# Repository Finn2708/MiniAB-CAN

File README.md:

# MiniAB-CAN
Toolhead board with CAN interface for [Voron Mini Afterburner](https://github.com/VoronDesign/Voron-0) and [Voron Stealthburner](https://github.com/VoronDesign/Voron-Afterburner/tree/sb-beta).

Features:
- CAN bus interface
- TMC2209 stepper driver for extruder motor
- Integrated ADXL345 for resonance compensation
- Neopixel Output for toolhead LEDs
- Two endstop and one probe port
- User-selectable fan voltages (5V/24V)

---

## Table of Contents
- [Prototype](#prototype)
  - [Size comparison](#size)
  - [Thermal images](#thermal-images)
- [Pinout](#pinout)
- [Interactive BOM](https://finn2708.github.io/MiniAB-CAN/index.html)

## Prototype

### Size

### Thermal images

## Pinout

## BOM
[Interactive BOM](https://finn2708.github.io/MiniAB-CAN/index.html)

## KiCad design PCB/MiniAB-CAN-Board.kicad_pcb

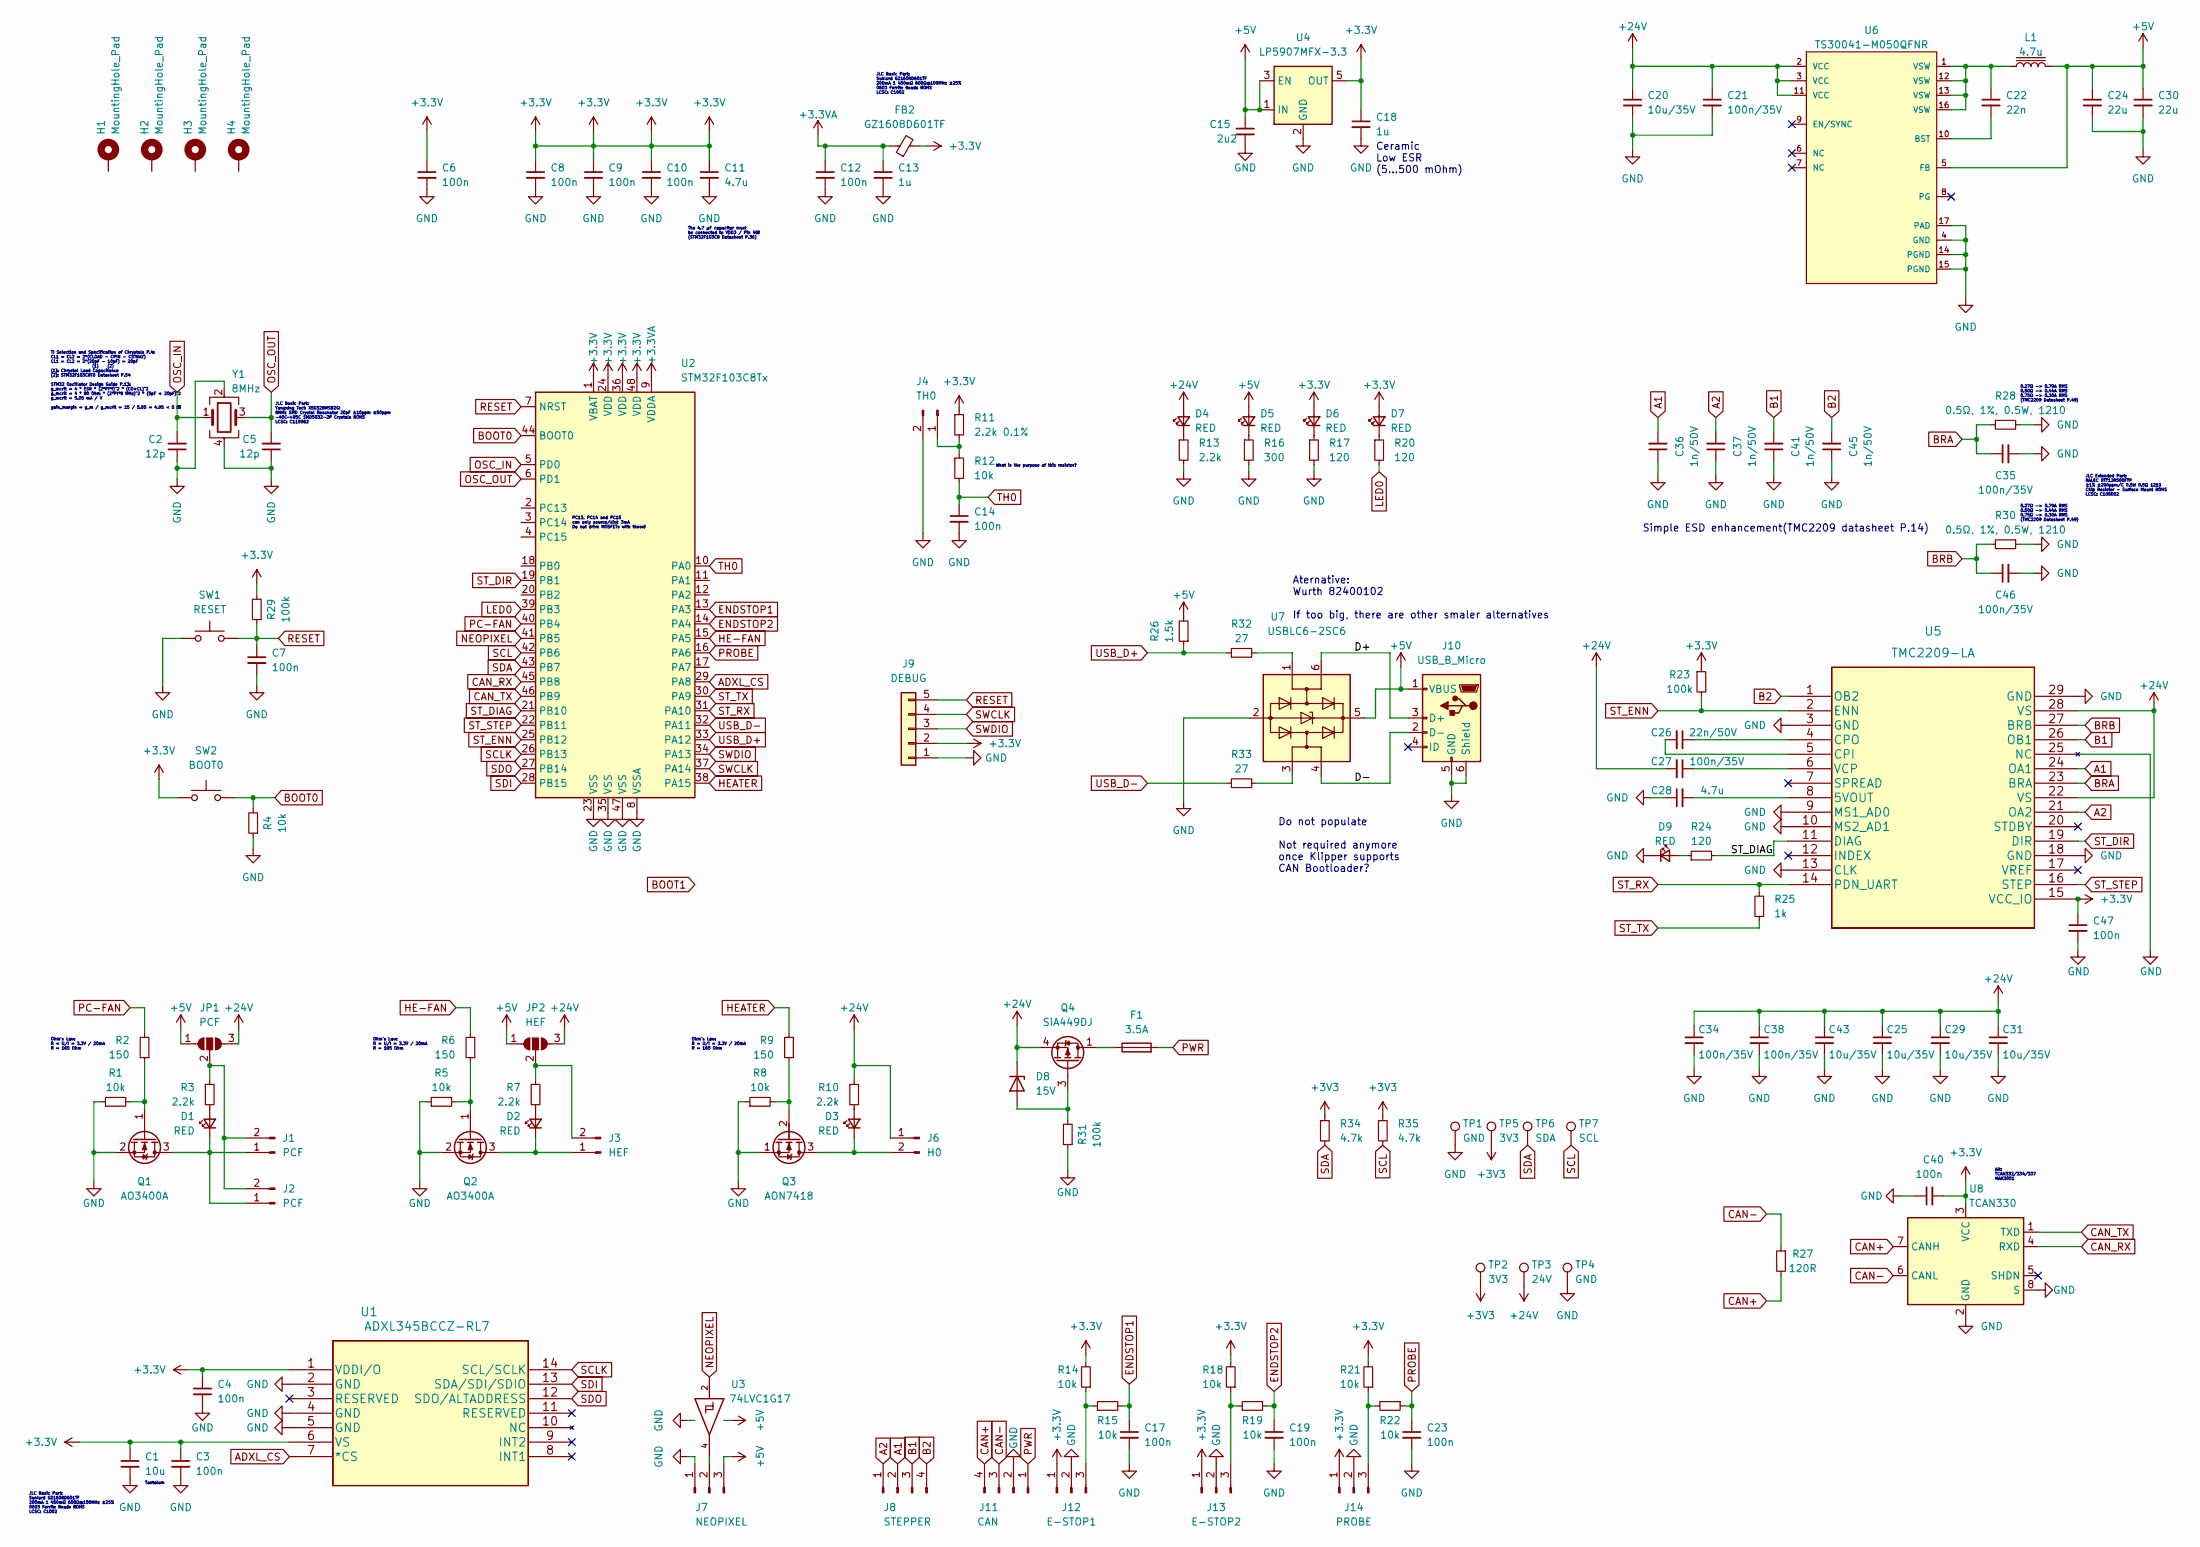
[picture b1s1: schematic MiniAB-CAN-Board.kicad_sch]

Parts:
C1: 10u; CP_EIA-3216-18_Kemet-A; MFG# TAJA106K016RNJ; LCSC# C7171
C2, C5: 12p; C_0402_1005Metric; MFG# C1005NP0120KGT; LCSC# C258502
C3, C4, C6, C7, C8, C9, C10, C12, C14, C17, C19, C23, C40, C47: 100n; C_0402_1005Metric; MFG# CL05B104KB54PNC; LCSC# C307331
C11, C28: 4.7u; C_0402_1005Metric; MFG# C0402X5R475M250NT; LCSC# C2911388
C13, C18: 1u; C_0402_1005Metric; MFG# CL05A105KA5NQNC; LCSC# C52923
C15: 2u2; C_0402_1005Metric; MFG# GRT155C71A225KE13D; LCSC# C415540
C20: 10u/35V; C_1206_3216Metric; MFG# GMK316AB7106KL-TR; LCSC# C454102
C21, C27, C34, C35, C38, C46: 100n/35V; C_0402_1005Metric; MFG# CL05B104KB54PNC; LCSC# C307331
C22: 22n; C_0402_1005Metric; MFG# CC0402KRX7R9BB223; LCSC# C107026
C24, C30: 22u; C_1206_3216Metric; MFG# C1206X7R226K160NT
C25, C29, C31, C43: 10u/35V; C_0805_2012Metric; MFG# C2012X5R1V226MT000E; LCSC# C338080
C26: 22n/50V; C_0402_1005Metric; MFG# 0402B223K500NT; LCSC# C1532
C36, C37, C41, C45: 1n/50V; C_0402_1005Metric; MFG# C0402C102K5RACAUTO; LCSC# C141053
D1, D2, D3, D4, D5, D6, D7, D9: RED; LED_0402_1005Metric
D8: 15V; D_SOD-323; MFG# SZMM3Z15VT1G; LCSC# C327522
F1: 3.5A; Fuse_0805_2012Metric; MFG# MFU0805FF03500P100; LCSC# C1972476
FB2: GZ1608D601TF; R_0603_1608Metric
H1, H2, H3, H4: MountingHole_Pad; MountingHole_3.2mm_M3_Pad_Via
J1, J2: PCF; JST_PH_B2B-PH-K_1x02_P2.00mm_Vertical
J3: HEF; JST_PH_B2B-PH-K_1x02_P2.00mm_Vertical
J4: TH0; JST_PH_B2B-PH-K_1x02_P2.00mm_Vertical
J6: H0; Molex_Micro-Fit_3.0_43045-0200_2x01_P3.00mm_Horizontal
J7: NEOPIXEL; JST_PH_B3B-PH-K_1x03_P2.00mm_Vertical
J8: STEPPER; JST_PH_B4B-PH-K_1x04_P2.00mm_Vertical
J9: DEBUG; PinHeader_1x05_P1.27mm_Vertical
J10: USB_B_Micro; USB_Micro-B_Amphenol_10118194_Horizontal
J11: CAN; Molex_Micro-Fit_3.0_43045-0400_2x02_P3.00mm_Horizontal
J12: E-STOP1; JST_PH_B3B-PH-K_1x03_P2.00mm_Vertical
J13: E-STOP2; JST_PH_B3B-PH-K_1x03_P2.00mm_Vertical
J14: PROBE; JST_PH_B3B-PH-K_1x03_P2.00mm_Vertical
JP1: PCF; SolderJumper-3_P1.3mm_Open_RoundedPad1.0x1.5mm_NumberLabels
JP2: HEF; SolderJumper-3_P1.3mm_Open_RoundedPad1.0x1.5mm_NumberLabels
L1: 4.7u; L_Coilcraft_XxL4020; MFG# MAPM0420F-4R7M-LF; LCSC# C280916
Q1, Q2: AO3400A; SOT-23
Q3: AON7418; MFG# AON7418; LCSC# C74384
Q4: SiA449DJ; Vishay_PowerPAK_SC70-6L_Single; MFG# SIA483DJ-T1-GE3; LCSC# C145467
R1, R4, R5, R8, R12, R14, R15, R18, R19, R21, R22: 10k; R_0402_1005Metric
R2, R6, R9: 150; R_0402_1005Metric
R3, R7, R10, R13: 2.2k; R_0402_1005Metric
R11: 2.2k 0.1%; R_0402_1005Metric
R16: 300; R_0402_1005Metric
R17, R20, R24: 120; R_0402_1005Metric
R23, R29, R31: 100k; R_0402_1005Metric
R25: 1k; R_0402_1005Metric
R26: 1.5k; R_0402_1005Metric; MFG# 0402WGJ0152TCE; LCSC# C25930
R27: 120R; R_0402_1005Metric; MFG# 0402WGF1200TCE; LCSC# C25079
R28, R30: 0.5Ω, 1%, 0.5W, 1210; R_0805_2012Metric
R32, R33: 27; R_0402_1005Metric; MFG# ERJ2RKF27R0X; LCSC# C413051
R34, R35: 4.7k; R_0402_1005Metric
SW1: RESET; SW_SPST_B3U-1000P; MFG# B3U-1000P; LCSC# C231329
SW2: BOOT0; SW_SPST_B3U-1000P; MFG# B3U-1000P; LCSC# C231329
TP1, TP4: GND; TestPoint_Pad_D1.0mm
TP2, TP5: 3V3; TestPoint_Pad_D1.0mm
TP3: 24V; TestPoint_Pad_D1.0mm
TP6: SDA; TestPoint_Pad_D1.0mm
TP7: SCL; TestPoint_Pad_D1.0mm
U1: ADXL345BCCZ-RL7
U2: STM32F103C8Tx; LQFP-48_7x7mm_P0.5mm
U3: 74LVC1G17; SOT-23-5
U4: LP5907MFX-3.3; SOT-23-5
U5: TMC2209-LA
U6: TS30041-M050QFNR; Semtech-QFN16-0-0-0; output voltage 5V; mouser part number 947-TS30041-M050QFNR; digikey description IC REG BUCK 5V 1A SYNC 16-VQFN
U7: USBLC6-2SC6; SOT-23-6; MFG# USBLC6-2SC6; LCSC# C7519
U8: TCAN330; TSOT-23-8
Y1: 8MHz; Crystal_SMD_3225-4Pin_3.2x2.5mm; MFG# TAXM8M4RFDCET2T; LCSC# C403948

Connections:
+3.3VA: C12.1, C13.1, FB2.1, U2.9 (VDDA)
+5V: C15.1, C24.1, C30.1, D5.2 (A), J7.3, J10.1 (VBUS), JP1.1 (A), JP2.1 (A), L1.2, R26.2, U3.5 (VCC), U4.1 (IN), U4.3 (EN), U6.5 (FB), U7.5 (VBUS)
+24V: C20.1, C21.1, C25.1, C27.2, C29.1, C31.1, C34.1, C38.1, C43.1, D4.2 (A), D8.1 (K), J6.1, JP1.3 (B), JP2.3 (B), Q4.4 (S), R10.1, TP3.1, U5.22 (VS), U5.28 (VS), U6.2 (VCC), U6.3 (VCC), U6.11 (VCC)
/D+: J10.3 (D+), U7.6 (I/O1)
/D-: J10.2 (D-), U7.4 (I/O2)
A1: C36.2, J8.2, U5.24 (OA1)
A2: C37.2, J8.1, U5.21 (OA2)
ADXL_CS: U1.7 (*CS), U2.29 (PA8)
B1: C41.2, J8.3, U5.26 (OB1)
B2: C45.2, J8.4, U5.1 (OB2)
BOOT0: R4.2, SW2.2, U2.44 (BOOT0)
BRA: C35.1, R28.2, U5.23 (BRA)
BRB: C46.1, R30.2, U5.27 (BRB)
CAN+: J11.4, R27.2, U8.7 (CANH)
CAN-: J11.3, R27.1, U8.6 (CANL)
CAN_RX: U2.45 (PB8), U8.4 (RXD)
CAN_TX: U2.46 (PB9), U8.1 (TXD)
ENDSTOP1: C17.1, R15.2, U2.13 (PA3)
ENDSTOP2: C19.1, R19.2, U2.14 (PA4)
GND: C1.2, C2.1, C3.2, C4.2, C5.1, C6.2, C7.2, C8.2, C9.2, C10.2, C11.2, C12.2, C13.2, C14.2, C15.2, C17.2, C18.2, C19.2, C20.2, C21.2, C23.2, C24.2, C25.2, C28.1, C29.2, C30.2, C31.2, C34.2, C35.2, C36.1, C37.1, C38.2, C40.1, C41.1, C43.2, C45.1, C46.2, C47.2, D9.1 (K), J4.2, J7.1, J9.1, J10.5 (GND), J10.6 (Shield), J11.2, J12.2, J13.2, J14.2, Q1.2 (S), Q2.2 (S), Q3.1 (S), R1.1, R4.1, R5.1, R8.1, R13.2, R16.2, R17.2, R28.1, R30.1, R31.1, SW1.1, TP1.1, TP4.1, U1.2 (GND), U1.4 (GND), U1.5 (GND), U2.8 (VSSA), U2.23 (VSS), U2.35 (VSS), U2.47 (VSS), U3.3 (GND), U4.2 (GND), U5.3 (GND), U5.9 (MS1_AD0), U5.10 (MS2_AD1), U5.13 (CLK), U5.18 (GND), U5.25 (NC), U5.29 (GND), U6.4 (GND), U6.14 (PGND), U6.15 (PGND), U6.17 (PAD), U7.2 (GND), U8.2 (GND), U8.8 (S), Y1.2, Y1.4
HE-FAN: R6.2, U2.15 (PA5)
HEATER: R9.2, U2.38 (PA15)
LED0: R20.2, U2.39 (PB3)
NEOPIXEL: U2.41 (PB5), U3.2
unnamed: C22.1, L1.1, U6.1 (VSW), U6.12 (VSW), U6.13 (VSW), U6.16 (VSW)
unnamed: C22.2, U6.10 (BST)
unnamed: C26.1, U5.4 (CPO)
unnamed: C26.2, U5.5 (CPI)
unnamed: C27.1, U5.6 (VCP)
unnamed: C28.2, U5.8 (5VOUT)
unnamed: D1.1 (K), J1.1, J2.1, Q1.3 (D)
unnamed: D1.2 (A), R3.2
unnamed: D2.1 (K), J3.1, Q2.3 (D)
unnamed: D2.2 (A), R7.2
unnamed: D3.1 (K), J6.2, Q3.3 (D)
unnamed: D3.2 (A), R10.2
unnamed: D4.1 (K), R13.1
unnamed: D5.1 (K), R16.1
unnamed: D6.1 (K), R17.1
unnamed: D7.1 (K), R20.1
unnamed: D8.2 (A), Q4.3 (G), R31.2
unnamed: D9.2 (A), R24.1
unnamed: F1.1, Q4.1 (D)
unnamed: J1.2, J2.2, JP1.2 (C), R3.1
unnamed: J3.2, JP2.2 (C), R7.1
unnamed: J4.1, R11.2, R12.1
unnamed: J7.2, U3.4
unnamed: J12.3, R14.1, R15.1
unnamed: J13.3, R18.1, R19.1
unnamed: J14.3, R21.1, R22.2
unnamed: Q1.1 (G), R1.2, R2.1
unnamed: Q2.1 (G), R5.2, R6.1
unnamed: Q3.2 (G), R8.2, R9.1
unnamed: R32.2, U7.1 (I/O1)
unnamed: R33.2, U7.3 (I/O2)
OSC_IN: C2.2, U2.5 (PD0), Y1.1
OSC_OUT: C5.2, U2.6 (PD1), Y1.3
PC-FAN: R2.2, U2.40 (PB4)
PROBE: C23.1, R22.1, U2.16 (PA6)
PWR: F1.2, J11.1
RESET: C7.1, J9.5, R29.1, SW1.2, U2.7 (NRST)
SCL: R35.2, TP7.1, U2.42 (PB6)
SCLK: U1.14 (SCL/SCLK), U2.26 (PB13)
SDA: R34.2, TP6.1, U2.43 (PB7)
SDI: U1.13 (SDA/SDI/SDIO), U2.28 (PB15)
SDO: U1.12 (SDO/ALTADDRESS), U2.27 (PB14)
ST_DIAG: R24.2, U2.21 (PB10), U5.11 (DIAG)
ST_DIR: U2.19 (PB1), U5.19 (DIR)
ST_ENN: R23.2, U2.25 (PB12), U5.2 (ENN)
ST_RX: R25.2, U2.31 (PA10), U5.14 (PDN_UART)
ST_STEP: U2.22 (PB11), U5.16 (STEP)
ST_TX: R25.1, U2.30 (PA9)
SWCLK: J9.4, U2.37 (PA14)
SWDIO: J9.3, U2.34 (PA13)
TH0: C14.1, R12.2, U2.10 (PA0)
USB_D+: R26.1, R32.1, U2.33 (PA12)
USB_D-: R33.1, U2.32 (PA11)

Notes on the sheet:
Ohm's Law: R = U/I = 3.3V / 20mA R = 165 Ohm
Do not populate Not required anymore once Klipper supports CAN Bootloader?
What is the purpose of this resistor?
0.27Ω -> 0.79A RMS 0.50Ω -> 0.44A RMS 0.75Ω -> 0.30A RMS (TMC2209 Datasheet P.49)
The 4.7 µF capacitor must be connected to VDD3 / Pin 48! (STM32F103C8 Datasheet P.36)
Alt: TCAN332/334/337 MAX3051
Tantalum
Aternative: Wurth 82400102 If too big, there are other smaler alternatives
JLC Basic Part: Sunlord GZ1608D601TF 200mA 1 450mΩ 600Ω@100MHz ±25% 0603 Ferrite Beads ROHS LCSC: C1002
PC13, PC14 and PC15 can only source/sink 3mA Do not drive MOSFETs with these!
Ceramic Low ESR (5...500 mOhm)
JLC Extended Part: RALEC RTT12R500FTP ±1% ±200ppm/C 0.5W 0.5Ω 1210 Chip Resistor - Surface Mount ROHS LCSC: C105052
TI Selection and Specification of Chrystals P.4: CL1 = CL2 = 2*(CLOAD - CPIN - CSTRAY) CL1 = CL2 = 2*(20pF - 10pF) = 20pF (1) (2) (1): Chrystal Load Capacitance (2): STM32F103C8T6 Datasheet P.54 STM32 Oscillator Design Guide P.13: g_mcrit = 4 * ESR * (2*PI*f)^2 * (C0+CL)^2 g_mcrit = 4 * 80 Ohm * (2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
JLC Basic Part: Yangxing Tech X50328MSB2GI 8MHz SMD Crystal Resonator 20pF ±10ppm ±50ppm -40C~+85C SMD5032-2P Crystals ROHS LCSC: C115962
Simple ESD enhancement(TMC2209 datasheet P.14)

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
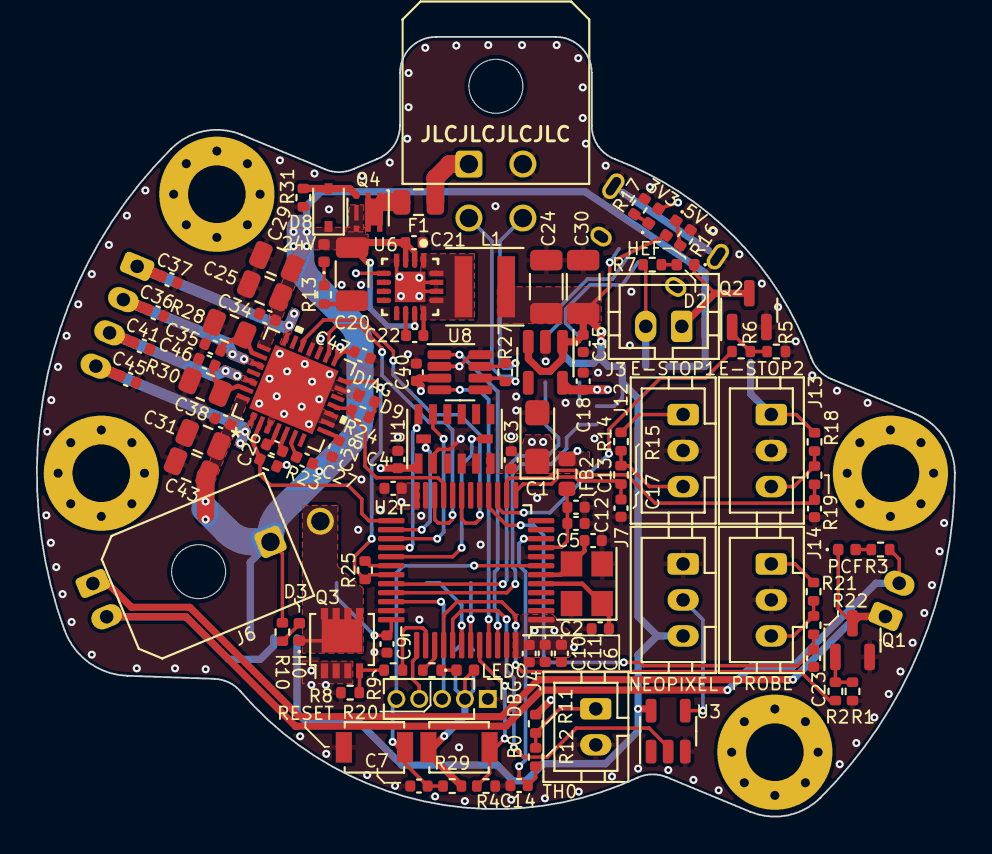
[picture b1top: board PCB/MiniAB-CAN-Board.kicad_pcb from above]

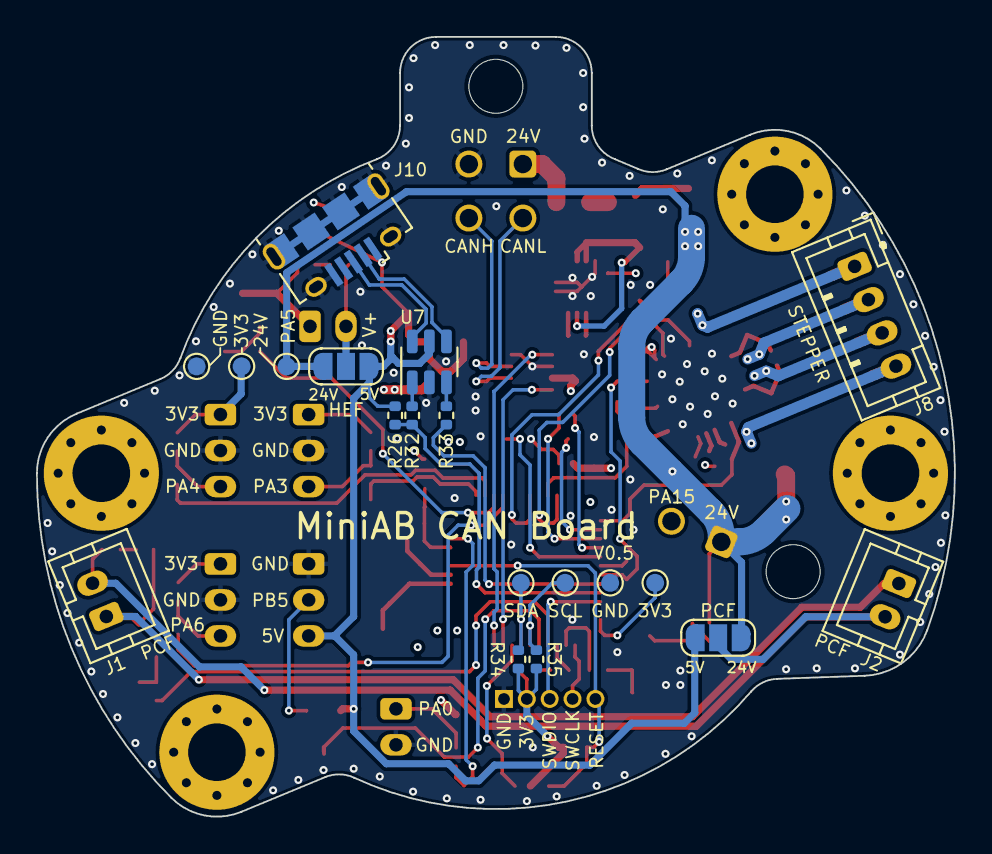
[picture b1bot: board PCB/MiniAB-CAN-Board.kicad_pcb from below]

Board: 4 copper layers, 51.0 x 43.3 mm, 129 parts (19 on the bottom side), 78 nets.

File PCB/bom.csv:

Comment,Designator,Footprint,LCSC
10u,C1,Capacitor_Tantalum_SMD:CP_EIA-3216-18_Kemet-A,
12p,"C2,C5",Capacitor_SMD:C_0402_1005Metric,
100n,"C3,C4,C6,C7,C8,C9,C10,C12,C14,C17,C19,C23,C40,C47",Capacitor_SMD:C_0402_1005Metric,
4.7u,"C11,C28",Capacitor_SMD:C_0402_1005Metric,
1u,"C13,C18",Capacitor_SMD:C_0402_1005Metric,
2u2,C15,Capacitor_SMD:C_0402_1005Metric,
10u/35V,C20,Capacitor_SMD:C_1206_3216Metric,
100n/35V,"C21,C27,C34,C35,C38,C46",Capacitor_SMD:C_0402_1005Metric,
22n,C22,Capacitor_SMD:C_0402_1005Metric,
22u,"C24,C30",Capacitor_SMD:C_1206_3216Metric,
10u/35V,"C25,C29,C31,C43",Capacitor_SMD:C_0805_2012Metric,
22n/50V,C26,Capacitor_SMD:C_0402_1005Metric,
1n/50V,"C36,C37,C41,C45",Capacitor_SMD:C_0402_1005Metric,
RED,"D1,D2,D3,D4,D5,D6,D7,D9",LED_SMD:LED_0402_1005Metric,
15V,D8,Diode_SMD:D_SOD-323,
3.5A,F1,Fuse:Fuse_0805_2012Metric,
GZ1608D601TF,FB2,Resistor_SMD:R_0603_1608Metric,
PCF,"J1,J2",Connector_JST:JST_PH_B2B-PH-K_1x02_P2.00mm_Vertical,
HEF,J3,Connector_JST:JST_PH_B2B-PH-K_1x02_P2.00mm_Vertical,
TH0,J4,Connector_JST:JST_PH_B2B-PH-K_1x02_P2.00mm_Vertical,
H0,J6,Connector_Molex:Molex_Micro-Fit_3.0_43045-0200_2x01_P3.00mm_Horizontal,
NEOPIXEL,J7,Connector_JST:JST_PH_B3B-PH-K_1x03_P2.00mm_Vertical,
STEPPER,J8,Connector_JST:JST_PH_B4B-PH-K_1x04_P2.00mm_Vertical,
DEBUG,J9,Connector_PinHeader_1.27mm:PinHeader_1x05_P1.27mm_Vertical,
USB_B_Micro,J10,Connector_USB:USB_Micro-B_Amphenol_10118194_Horizontal,
CAN,J11,Connector_Molex:Molex_Micro-Fit_3.0_43045-0400_2x02_P3.00mm_Horizontal,
E-STOP1,J12,Connector_JST:JST_PH_B3B-PH-K_1x03_P2.00mm_Vertical,
E-STOP2,J13,Connector_JST:JST_PH_B3B-PH-K_1x03_P2.00mm_Vertical,
PROBE,J14,Connector_JST:JST_PH_B3B-PH-K_1x03_P2.00mm_Vertical,
4.7u,L1,Inductor_SMD:L_Coilcraft_XxL4020,
AO3400A,"Q1,Q2",Package_TO_SOT_SMD:SOT-23,
AON7418,Q3,footprints:AON7418,
SiA449DJ,Q4,Package_TO_SOT_SMD:Vishay_PowerPAK_SC70-6L_Single,
10k,"R1,R4,R5,R8,R12,R14,R15,R18,R19,R21,R22",Resistor_SMD:R_0402_1005Metric,
150,"R2,R6,R9",Resistor_SMD:R_0402_1005Metric,
2.2k,"R3,R7,R10,R13",Resistor_SMD:R_0402_1005Metric,
2.2k 0.1%,R11,Resistor_SMD:R_0402_1005Metric,
300,R16,Resistor_SMD:R_0402_1005Metric,
120,"R17,R20,R24",Resistor_SMD:R_0402_1005Metric,
100k,"R23,R29,R31",Resistor_SMD:R_0402_1005Metric,
1k,R25,Resistor_SMD:R_0402_1005Metric,
1.5k,R26,Resistor_SMD:R_0402_1005Metric,
120R,R27,Resistor_SMD:R_0402_1005Metric,
"0.5Ω, 1%, 0.5W, 1210","R28,R30",Resistor_SMD:R_0805_2012Metric,
27,"R32,R33",Resistor_SMD:R_0402_1005Metric,
4.7k,"R34,R35",Resistor_SMD:R_0402_1005Metric,
RESET,SW1,Button_Switch_SMD:SW_SPST_B3U-1000P,
BOOT0,SW2,Button_Switch_SMD:SW_SPST_B3U-1000P,
ADXL345BCCZ-RL7,U1,footprints:ADXL345BCCZ-RL7,
STM32F103C8Tx,U2,Package_QFP:LQFP-48_7x7mm_P0.5mm,
74LVC1G17,U3,Package_TO_SOT_SMD:SOT-23-5,
LP5907MFX-3.3,U4,Package_TO_SOT_SMD:SOT-23-5,
TMC2209-LA,U5,footprints:TMC2209-LA,
TS30041-M050QFNR,U6,TS30041:Semtech-QFN16-0-0-0,
USBLC6-2SC6,U7,Package_TO_SOT_SMD:SOT-23-6,
TCAN330,U8,Package_TO_SOT_SMD:TSOT-23-8,
8MHz,Y1,Crystal:Crystal_SMD_3225-4Pin_3.2x2.5mm,

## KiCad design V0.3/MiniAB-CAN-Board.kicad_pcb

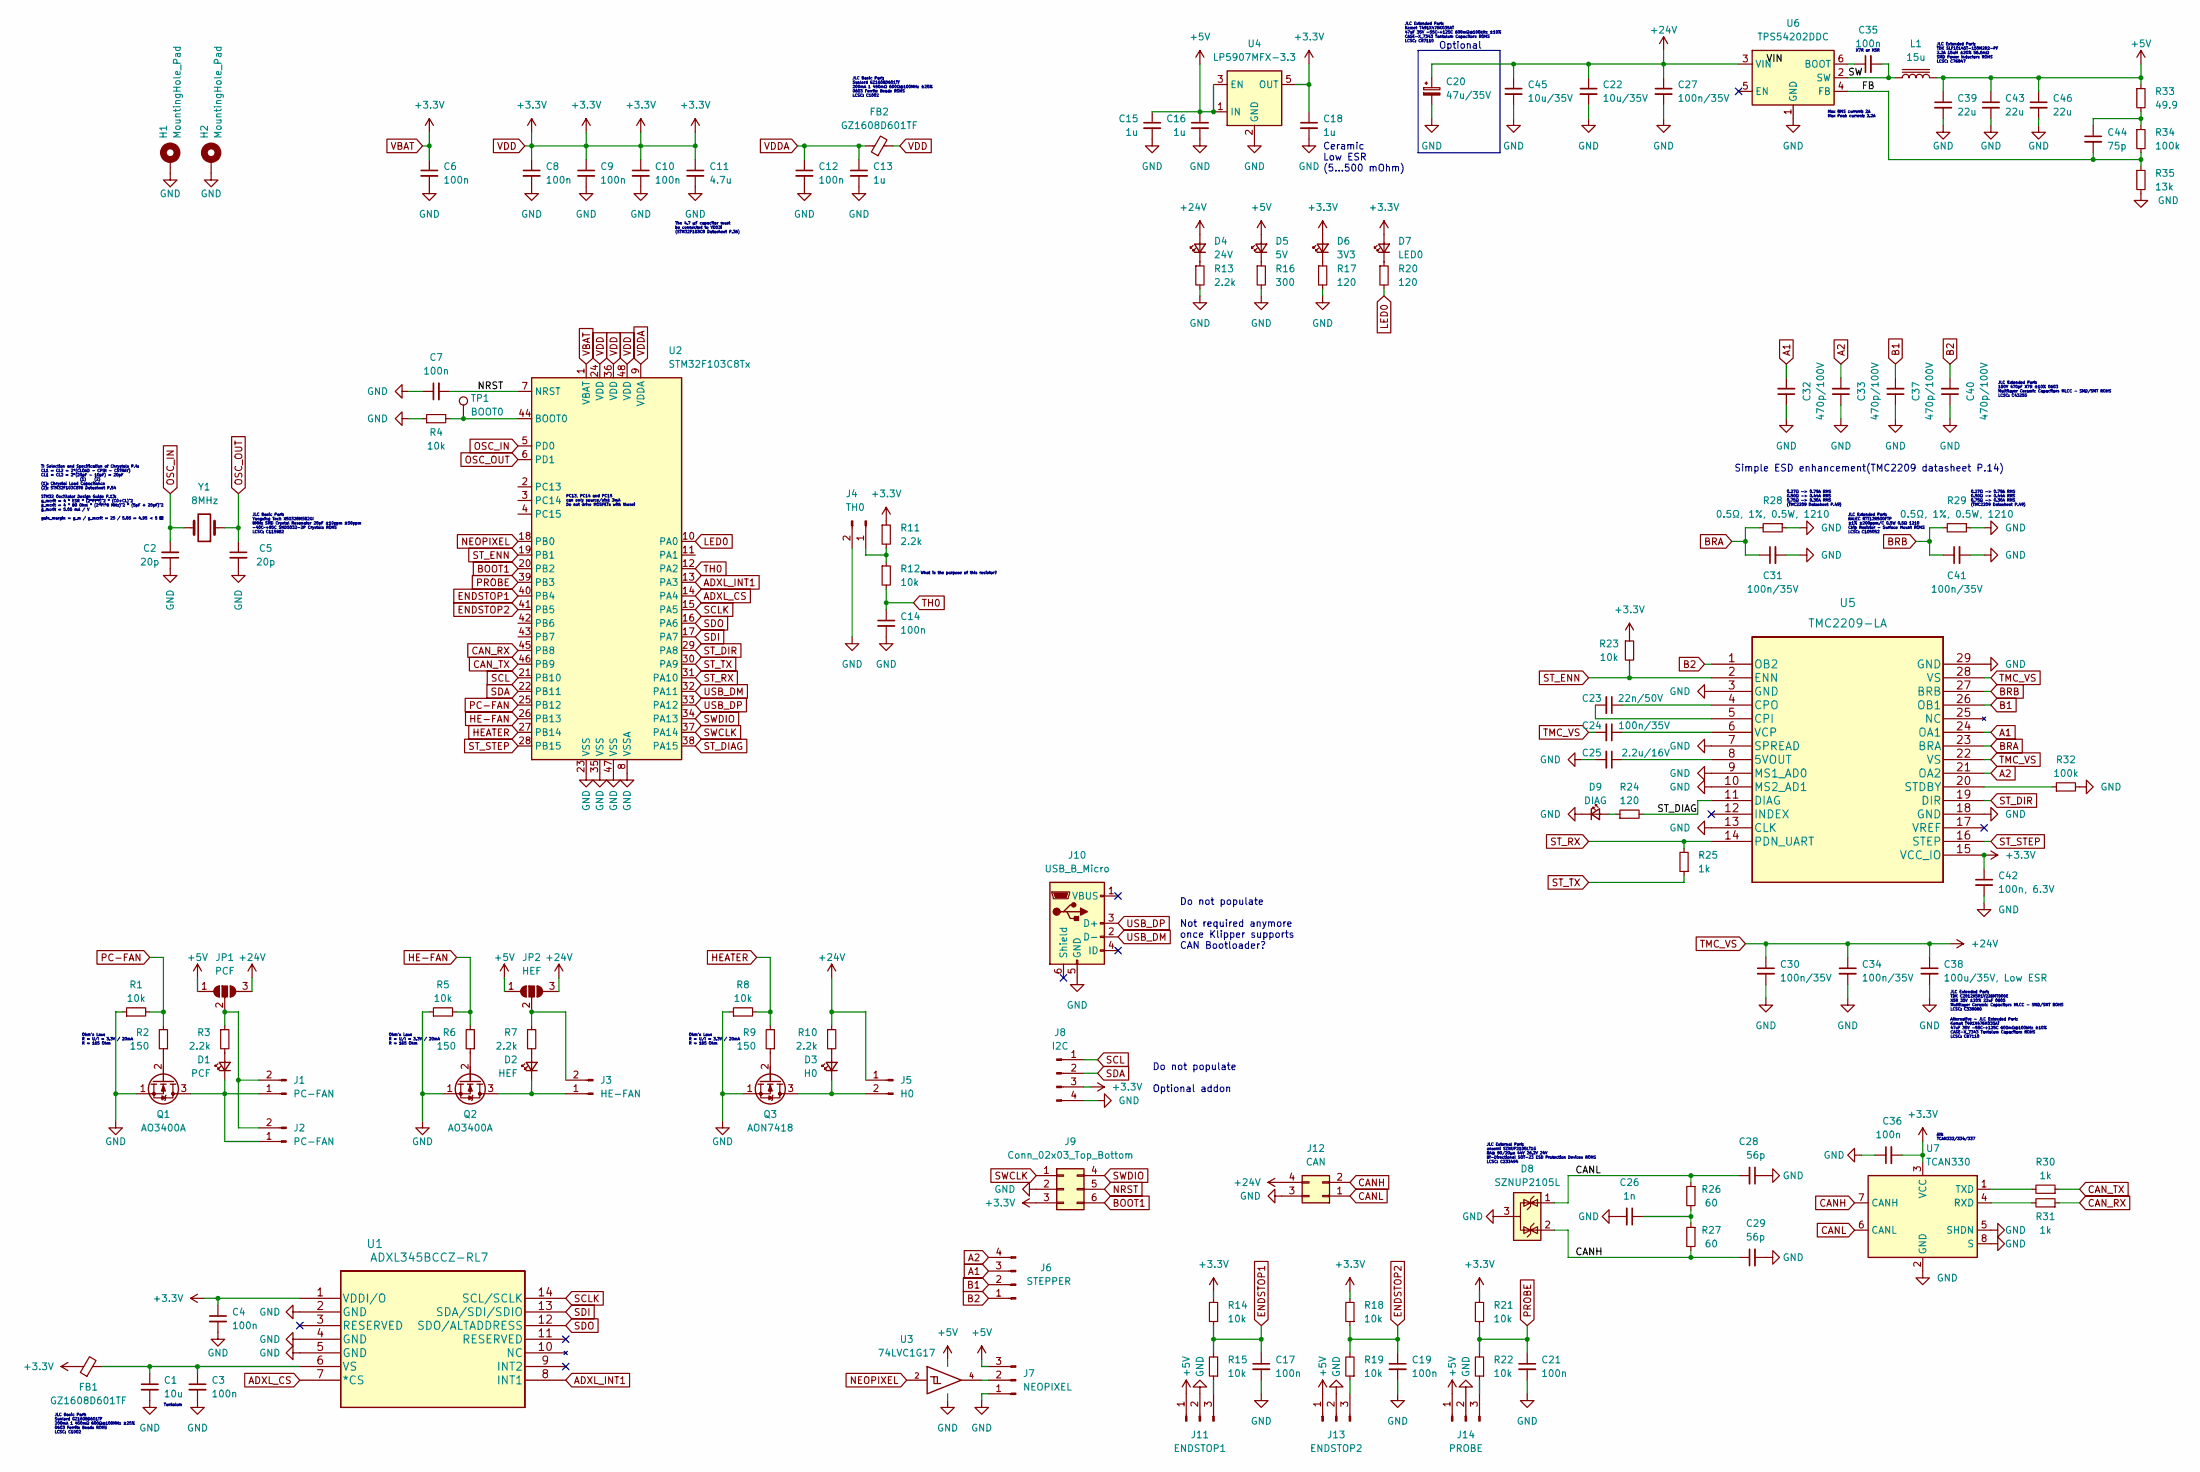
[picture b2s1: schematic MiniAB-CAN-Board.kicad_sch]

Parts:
C1: 10u; CP_EIA-3216-18_Kemet-A
C2, C5: 20p; C_0402_1005Metric
C3, C4, C6, C7, C8, C9, C10, C12, C14, C17, C19, C21, C35, C36: 100n; C_0402_1005Metric
C11: 4.7u; C_0402_1005Metric
C13, C15, C16, C18: 1u; C_0402_1005Metric
C20: 47u/35V; CP_EIA-7343-43_Kemet-X
C22, C45: 10u/35V; C_0805_2012Metric
C23: 22n/50V; C_0402_1005Metric
C24, C27, C30, C31, C34, C41: 100n/35V; C_0402_1005Metric
C25: 2.2u/16V; C_0603_1608Metric
C26: 1n; C_0402_1005Metric
C28, C29: 56p; C_0402_1005Metric
C32, C33, C37, C40: 470p/100V; C_0603_1608Metric
C38: 100u/35V, Low ESR; C_0805_2012Metric
C39, C43, C46: 22u; C_0805_2012Metric
C42: 100n, 6.3V; C_0402_1005Metric
C44: 75p; C_0402_1005Metric
D1: PCF; LED_0402_1005Metric
D2: HEF; LED_0402_1005Metric
D3: H0; LED_0402_1005Metric
D4: 24V; LED_0402_1005Metric
D5: 5V; LED_0402_1005Metric
D6: 3V3; LED_0402_1005Metric
D7: LED0; LED_0402_1005Metric
D8: SZNUP2105L; SOT-23
D9: DIAG; LED_0402_1005Metric
FB1, FB2: GZ1608D601TF; R_0603_1608Metric
H1, H2: MountingHole_Pad; MountingHole_3.2mm_M3_Pad_Via
J1, J2: PC-FAN; JST_PH_B2B-PH-K_1x02_P2.00mm_Vertical
J3: HE-FAN; JST_PH_B2B-PH-SM4-TB_1x02-1MP_P2.00mm_Vertical
J4: TH0; JST_PH_B2B-PH-SM4-TB_1x02-1MP_P2.00mm_Vertical
J5: H0; Molex_Micro-Fit_3.0_43045-0200_2x01_P3.00mm_Horizontal
J6: STEPPER; JST_PH_B4B-PH-K_1x04_P2.00mm_Vertical
J7: NEOPIXEL; JST_PH_B3B-PH-SM4-TB_1x03-1MP_P2.00mm_Vertical
J8: I2C; JST_PH_B4B-PH-SM4-TB_1x04-1MP_P2.00mm_Vertical
J9: Conn_02x03_Top_Bottom; PinHeader_2x03_P1.27mm_Vertical_SMD
J10: USB_B_Micro; USB_Micro-B_Molex-105133-0001
J11: ENDSTOP1; JST_PH_B3B-PH-SM4-TB_1x03-1MP_P2.00mm_Vertical
J12: CAN; Molex_Micro-Fit_3.0_43045-0400_2x02_P3.00mm_Horizontal
J13: ENDSTOP2; JST_PH_B3B-PH-SM4-TB_1x03-1MP_P2.00mm_Vertical
J14: PROBE; JST_PH_B3B-PH-SM4-TB_1x03-1MP_P2.00mm_Vertical
JP1: PCF; SolderJumper-3_P1.3mm_Open_RoundedPad1.0x1.5mm_NumberLabels
JP2: HEF; SolderJumper-3_P1.3mm_Open_RoundedPad1.0x1.5mm_NumberLabels
L1: 15u; L_TDK_SLF10145
Q1, Q2: AO3400A; SOT-23
Q3: AON7418
R1, R4, R5, R8, R12, R14, R15, R18, R19, R21, R22, R23: 10k; R_0402_1005Metric
R2, R6, R9: 150; R_0402_1005Metric
R3, R7, R10, R11, R13: 2.2k; R_0402_1005Metric
R16: 300; R_0402_1005Metric
R17, R20, R24: 120; R_0402_1005Metric
R25, R30, R31: 1k; R_0402_1005Metric
R26, R27: 60; R_0603_1608Metric
R28, R29: 0.5Ω, 1%, 0.5W, 1210; R_1210_3225Metric
R32: 100k; R_0402_1005Metric
R33: 49.9; R_0402_1005Metric
R34: 100k; R_0603_1608Metric
R35: 13k; R_0603_1608Metric
TP1: BOOT0; TestPoint_Pad_D1.0mm
U1: ADXL345BCCZ-RL7
U2: STM32F103C8Tx; LQFP-48_7x7mm_P0.5mm
U3: 74LVC1G17; SOT-23-5
U4: LP5907MFX-3.3; SOT-23-5
U5: TMC2209-LA
U6: TPS54202DDC; SOT-23-6
U7: TCAN330; TSOT-23-8
Y1: 8MHz; Crystal_SMD_5032-2Pin_5.0x3.2mm

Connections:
+5V: C15.1, C16.1, C39.1, C43.1, C46.1, D5.2 (A), J7.3, J11.1, J13.1, J14.1, JP1.1 (A), JP2.1 (A), L1.2, R33.1, U3.5 (VCC), U4.1 (IN), U4.3 (EN)
/FB: C44.2, R34.2, R35.1, U6.4 (FB)
/SW: C35.2, L1.1, U6.2 (SW)
A1: C32.2, J6.3, U5.24 (OA1)
A2: C33.2, J6.4, U5.21 (OA2)
ADXL_CS: U1.7 (*CS), U2.14 (PA4)
ADXL_INT1: U1.8 (INT1), U2.13 (PA3)
B1: C37.2, J6.2, U5.26 (OB1)
B2: C40.2, J6.1, U5.1 (OB2)
BOOT1: J9.6, U2.20 (PB2)
BRA: C31.1, R28.2, U5.23 (BRA)
BRB: C41.1, R29.2, U5.27 (BRB)
CANH: C29.1, D8.2 (K), J12.2, R27.2, U7.7 (CANH)
CANL: C28.2, D8.1 (K), J12.1, R26.1, U7.6 (CANL)
CAN_RX: R31.1, U2.45 (PB8)
CAN_TX: R30.1, U2.46 (PB9)
ENDSTOP1: C17.1, R14.1, R15.2, U2.40 (PB4)
ENDSTOP2: C19.1, R18.1, R19.2, U2.41 (PB5)
GND: C1.2, C2.1, C3.2, C4.2, C5.2, C6.2, C7.1, C8.2, C9.2, C10.2, C11.2, C12.2, C13.2, C14.2, C15.2, C16.2, C17.2, C18.2, C19.2, C20.2, C21.2, C22.2, C25.2, C26.2, C27.2, C28.1, C29.2, C30.2, C31.2, C32.1, C33.1, C34.2, C36.1, C37.1, C38.2, C39.2, C40.1, C41.2, C42.2, C43.2, C45.2, C46.2, D8.3 (A), D9.1 (K), H1.1, H2.1, J4.2, J7.1, J8.4, J9.2, J10.5 (GND), J11.2, J12.3, J13.2, J14.2, Q1.1 (S), Q2.1 (S), Q3.1 (S), R1.1, R4.1, R5.1, R8.1, R13.2, R16.2, R17.2, R28.1, R29.1, R32.2, R35.2, U1.2 (GND), U1.4 (GND), U1.5 (GND), U2.8 (VSSA), U2.23 (VSS), U2.35 (VSS), U2.47 (VSS), U3.3 (GND), U4.2 (GND), U5.3 (GND), U5.7 (SPREAD), U5.9 (MS1_AD0), U5.10 (MS2_AD1), U5.13 (CLK), U5.18 (GND), U5.29 (GND), U6.1 (GND), U7.2 (GND), U7.5 (SHDN), U7.8 (S)
HE-FAN: R5.2, R6.2, U2.26 (PB13)
HEATER: R8.2, R9.2, U2.27 (PB14)
LED0: R20.2, U2.10 (PA0)
NEOPIXEL: U2.18 (PB0), U3.2
NRST: C7.2, J9.5, U2.7 (NRST)
unnamed: C1.1, C3.1, FB1.2, U1.6 (VS)
unnamed: C23.1, U5.4 (CPO)
unnamed: C23.2, U5.5 (CPI)
unnamed: C24.1, U5.6 (VCP)
unnamed: C25.1, U5.8 (5VOUT)
unnamed: C26.1, R26.2, R27.1
unnamed: C35.1, U6.6 (BOOT)
unnamed: C44.1, R33.2, R34.1
unnamed: D1.1 (K), J1.1, J2.1, Q1.3 (D)
unnamed: D1.2 (A), R3.2
unnamed: D2.1 (K), J3.1, Q2.3 (D)
unnamed: D2.2 (A), R7.2
unnamed: D3.1 (K), J5.2, Q3.3 (D)
unnamed: D3.2 (A), R10.2
unnamed: D4.1 (K), R13.1
unnamed: D5.1 (K), R16.1
unnamed: D6.1 (K), R17.1
unnamed: D7.1 (K), R20.1
unnamed: D9.2 (A), R24.1
unnamed: J1.2, J2.2, JP1.2 (C), R3.1
unnamed: J3.2, JP2.2 (C), R7.1
unnamed: J4.1, R11.2, R12.1
unnamed: J7.2, U3.4
unnamed: J11.3, R15.1
unnamed: J13.3, R19.1
unnamed: J14.3, R22.1
unnamed: Q1.2 (G), R2.1
unnamed: Q2.2 (G), R6.1
unnamed: Q3.2 (G), R9.1
unnamed: R4.2, TP1.1, U2.44 (BOOT0)
unnamed: R30.2, U7.1 (TXD)
unnamed: R31.2, U7.4 (RXD)
unnamed: R32.1, U5.20 (STDBY)
OSC_IN: C2.2, U2.5 (PD0), Y1.2
OSC_OUT: C5.1, U2.6 (PD1), Y1.1
PC-FAN: R1.2, R2.2, U2.25 (PB12)
PROBE: C21.1, R21.1, R22.2, U2.39 (PB3)
SCL: J8.1, U2.21 (PB10)
SCLK: U1.14 (SCL/SCLK), U2.15 (PA5)
SDA: J8.2, U2.22 (PB11)
SDI: U1.13 (SDA/SDI/SDIO), U2.17 (PA7)
SDO: U1.12 (SDO/ALTADDRESS), U2.16 (PA6)
ST_DIAG: R24.2, U2.38 (PA15), U5.11 (DIAG)
ST_DIR: U2.29 (PA8), U5.19 (DIR)
ST_ENN: R23.2, U2.19 (PB1), U5.2 (ENN)
ST_RX: R25.2, U2.31 (PA10), U5.14 (PDN_UART)
ST_STEP: U2.28 (PB15), U5.16 (STEP)
ST_TX: R25.1, U2.30 (PA9)
SWCLK: J9.1, U2.37 (PA14)
SWDIO: J9.4, U2.34 (PA13)
TH0: C14.1, R12.2, U2.12 (PA2)
TMC_VS: C20.1, C22.1, C24.2, C27.1, C30.1, C34.1, C38.1, C45.1, D4.2 (A), J5.1, J12.4, JP1.3 (B), JP2.3 (B), R10.1, U5.22 (VS), U5.28 (VS), U6.3 (VIN)
USB_DM: J10.2 (D-), U2.32 (PA11)
USB_DP: J10.3 (D+), U2.33 (PA12)
VBAT: C4.1, C6.1, C8.1, C9.1, C10.1, C11.1, C18.1, C36.2, C42.1, D6.2 (A), D7.2 (A), FB1.1, FB2.2, J8.3, J9.3, R11.1, R14.2, R18.2, R21.2, R23.1, U1.1 (VDDI/O), U2.1 (VBAT), U2.24 (VDD), U2.36 (VDD), U2.48 (VDD), U4.5 (OUT), U5.15 (VCC_IO), U7.3 (VCC)
VDDA: C12.1, C13.1, FB2.1, U2.9 (VDDA)

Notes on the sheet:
Do not populate Optional addon
Ohm's Law: R = U/I = 3.3V / 20mA R = 165 Ohm
JLC Extended Part: TDK C2012X5R1V226MT000E X5R 35V ±20% 22uF 0805 Multilayer Ceramic Capacitors MLCC - SMD/SMT ROHS LCSC: C338080
Optional
Do not populate Not required anymore once Klipper supports CAN Bootloader?
What is the purpose of this resistor?
0.27Ω -> 0.79A RMS 0.50Ω -> 0.44A RMS 0.75Ω -> 0.30A RMS (TMC2209 Datasheet P.49)
The 4.7 µF capacitor must be connected to VDD3! (STM32F103C8 Datasheet P.36)
Alt: TCAN332/334/337
Tantalum
JLC Extended Part: Kemet T491X476K035AT 47uF 35V -55C~+125C 600mΩ@100kHz ±10% CASE-X_7343 Tantalum Capacitors ROHS LCSC: C87110
JLC Basic Part: Sunlord GZ1608D601TF 200mA 1 450mΩ 600Ω@100MHz ±25% 0603 Ferrite Beads ROHS LCSC: C1002
PC13, PC14 and PC15 can only source/sink 3mA Do not drive MOSFETs with these!
Ceramic Low ESR (5...500 mOhm)
JLC Extended Part: RALEC RTT12R500FTP ±1% ±200ppm/C 0.5W 0.5Ω 1210 Chip Resistor - Surface Mount ROHS LCSC: C105052
TI Selection and Specification of Chrystals P.4: CL1 = CL2 = 2*(CLOAD - CPIN - CSTRAY) CL1 = CL2 = 2*(20pF - 10pF) = 20pF (1) (2) (1): Chrystal Load Capacitance (2): STM32F103C8T6 Datasheet P.54 STM32 Oscillator Design Guide P.13: g_mcrit = 4 * ESR * (2*PI*f)^2 * (C0+CL)^2 g_mcrit = 4 * 80 Ohm * (2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
Alternative - JLC Extended Part: Kemet T491X476K035AT 47uF 35V -55C~+125C 600mΩ@100kHz ±10% CASE-X_7343 Tantalum Capacitors ROHS LCSC: C87110
JLC Extended Part: 100V 470pF X7R ±10% 0603 Multilayer Ceramic Capacitors MLCC - SMD/SMT ROHS LCSC: C43255
X7R or X5R
Max RMS current: 2A Max Peak current: 2.2A
JLC Basic Part: Yangxing Tech X50328MSB2GI 8MHz SMD Crystal Resonator 20pF ±10ppm ±50ppm -40C~+85C SMD5032-2P Crystals ROHS LCSC: C115962
JLC Extended Part: TDK SLF10145T-150M2R2-PF 2.2A 15uH ±20% 56.6mΩ SMD Power Inductors ROHS LCSC: C76847
JLC External Part: onsemi SZNUP2105LT1G 8A@ 80/20μs 44V 26.2V 24V Bi-Directional SOT-23 ESD Protection Devices ROHS LCSC: C233494
Simple ESD enhancement(TMC2209 datasheet P.14)

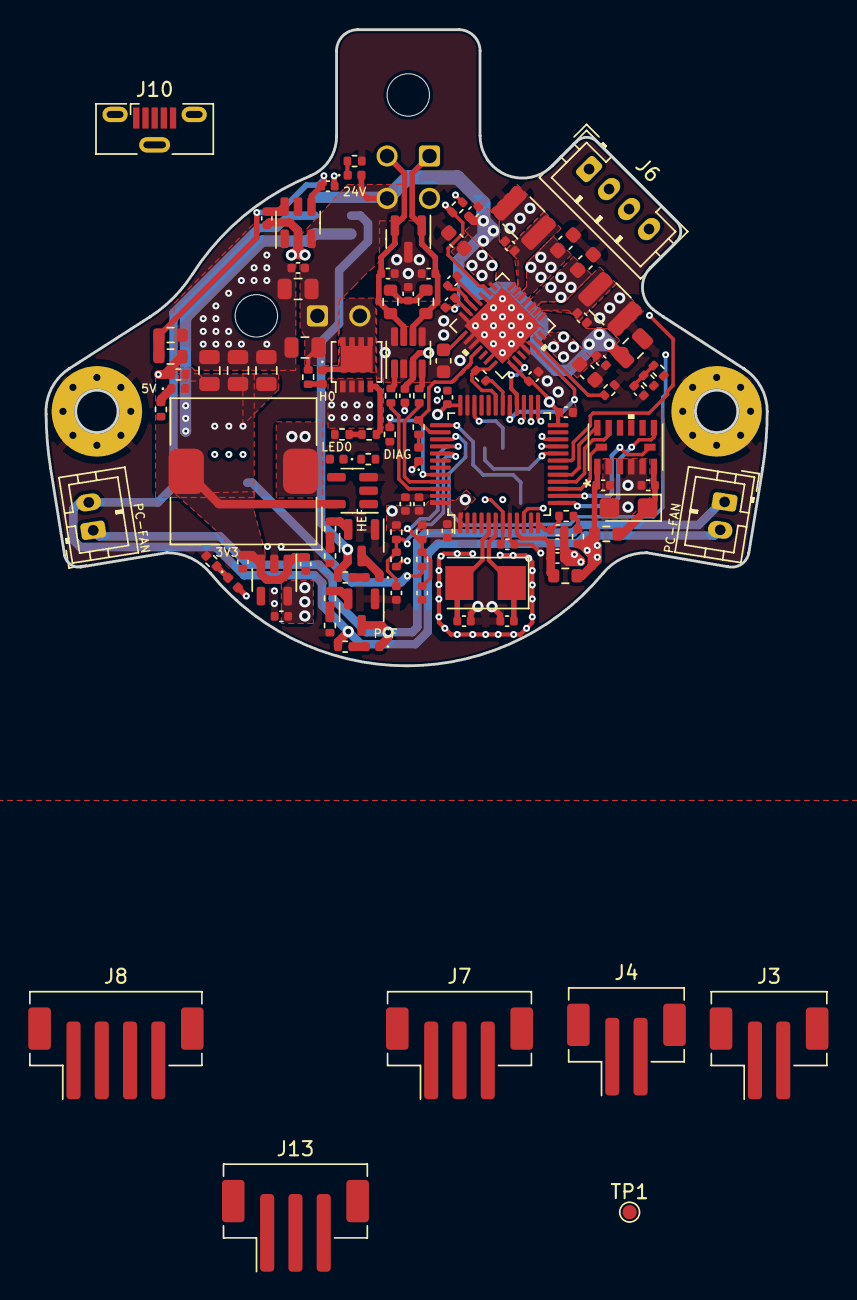
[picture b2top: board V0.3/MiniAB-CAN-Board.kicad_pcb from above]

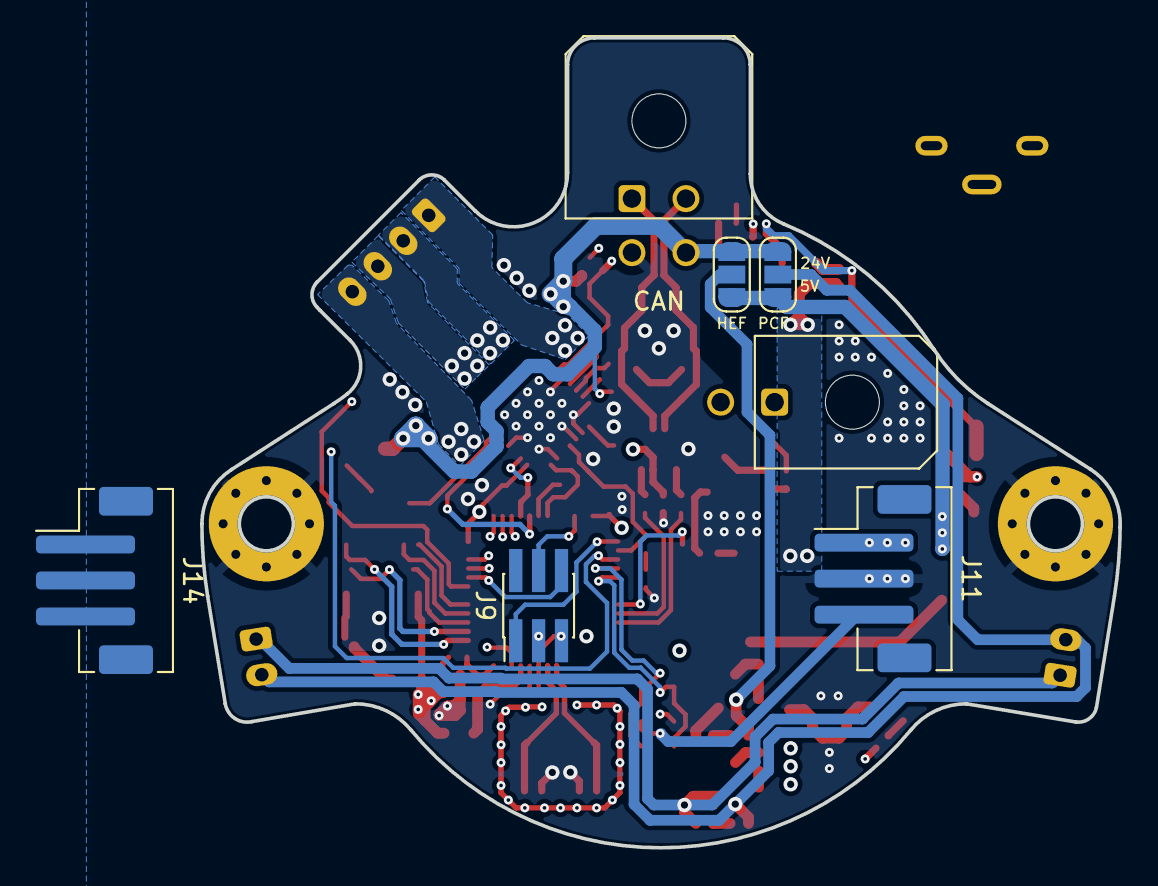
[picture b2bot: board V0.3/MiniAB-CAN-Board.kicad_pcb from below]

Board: 4 copper layers, 51.0 x 45.0 mm, 122 parts (7 on the bottom side), 80 nets.

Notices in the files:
parts and their libraries:
Copyright 2021 Accelerated Designs. All rights reserved.
